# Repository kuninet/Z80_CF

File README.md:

# Z80マイコン コンパクトフラッシュアダプタボード (KZ80-CF)

- SBC8080バスにつながるコンパクトフラッシュボード のデータ類です。
  - [128kB SRAMボード(KZ80-1MSRAM)](https://github.com/kuninet/Z80_1MRAMB)と組み合わせてCP/Mを動かす際に使用できます。
- 詳しい情報は以下のwikiページをご覧ください
  - https://github.com/kuninet/Z80_CF/wiki

## 回路図

[PDF版回路図はこちら](img/SBC80-CF.pdf)

## 部品表

- 部品表は以下にあります。OpenOffice等のcalcで開ける形式です
  - https://github.com/kuninet/Z80_CF/blob/master/KiCAD/SBC80-CF.ods

## 注意点

- REV1基板はコネクタのピンが誤って逆になっているため、CFカードの表裏を逆に挿入する必要があります。(ガイドのレールを削らないとうまくささりません) REV2では改善しています。
- CFカードコネクタは、REV1では秋月電子で手に入るネジ幅40mmのタイプを使用していますが、REV2ではマルツパーツ、aitendoで手に入るネジ幅38.78mmのタイプへ変更しています。

## ライセンス

- 本リポジトリのデータは MIT License のもとで公開します。

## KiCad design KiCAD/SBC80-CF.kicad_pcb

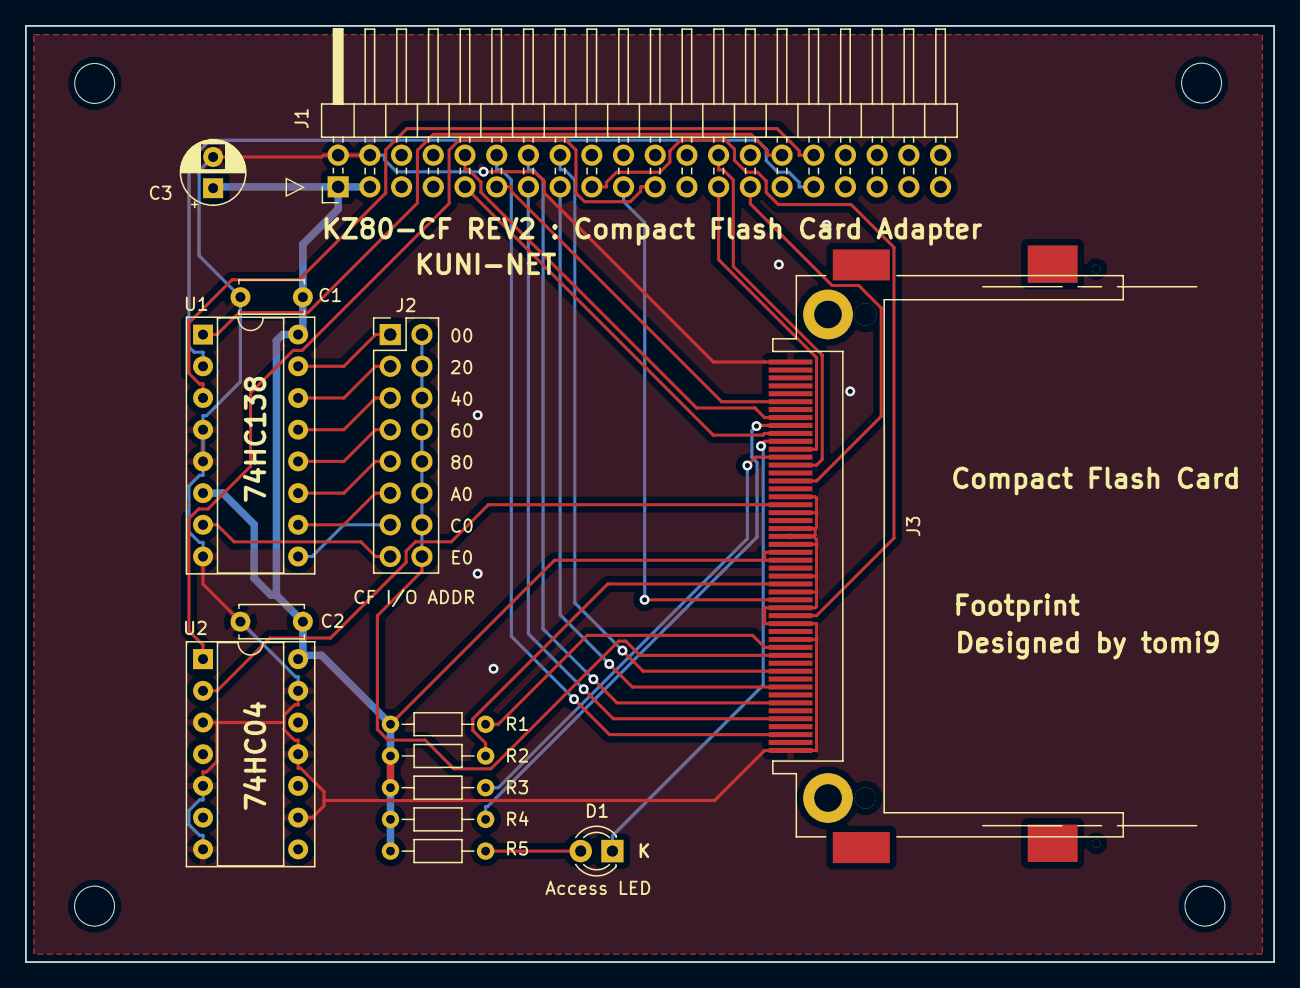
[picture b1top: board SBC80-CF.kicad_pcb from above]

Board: 2 copper layers, 100.0 x 75.0 mm, 18 parts (0 on the bottom side), 35 nets.

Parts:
C1, C2: 0.1u; C_Disc_D5.0mm_W2.5mm_P5.00mm
C3: 10u; CP_Radial_D5.0mm_P2.50mm
D1: LED; LED_D3.0mm
J1: Conn_02x20_Odd_Even; PinHeader_2x20_P2.54mm_Horizontal
J2: I/O ADDR JP; PinHeader_2x08_P2.54mm_Vertical
J3: CF Card Conn; CF-50P
MH1, MH2, MH3, MH4: MountingHole; MountingHole_3.2mm_M3
R1, R2, R3, R4, R5: 1k; R_Axial_DIN0204_L3.6mm_D1.6mm_P7.62mm_Horizontal
U1: 74HC138; DIP-16_W7.62mm_Socket
U2: 74HC04; DIP-14_W7.62mm_Socket

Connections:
/A0: J1.25, J3.20
/A1: J1.26, J3.19
/A2: J1.27, J3.18
/A5: J1.30, U1.1
/A6: J1.31, U1.2
/A7: J1.32, U1.3
/D0: J1.9, J3.21
/D1: J1.10, J3.22
/D2: J1.11, J3.23
/D3: J1.12, J3.2
/D4: J1.13, J3.3
/D5: J1.14, J3.4
/D6: J1.15, J3.5
/D7: J1.16, J3.6
/RES: J1.21, U2.1
/~CS0: J2.2, J2.4, J2.6, J2.8, J2.10, J2.12, J2.14, J2.16, J3.7
/~CS1: J3.32, R1.2
/~DASP: D1.1, J3.45
/~DMACK: J3.44, R3.2
/~PDIAG: J3.46, R4.2
/~WE: J3.36, R2.2
GND: C1.2, C2.2, C3.2, J1.2, J1.4, J3.1, J3.8, J3.9, J3.10, J3.11, J3.12, J3.14, J3.15, J3.16, J3.17, J3.39, J3.50, U1.4, U1.5, U1.8, U2.3, U2.5, U2.7, U2.9, U2.11, U2.13
unnamed: D1.2, R5.2
unnamed: J2.1, U1.15
unnamed: J2.3, U1.14
unnamed: J2.5, U1.13
unnamed: J2.7, U1.12
unnamed: J2.9, U1.11
unnamed: J2.11, U1.10
unnamed: J2.13, U1.9
unnamed: J2.15, U1.7
VCC: C1.1, C2.1, C3.1, J1.1, J1.3, J3.13, J3.38, R1.1, R2.1, R3.1, R4.1, R5.1, U1.6, U1.16, U2.14
~IORD: J1.17, J3.34
~IOWR: J1.19, J3.35
~RESET: J3.41, U2.2

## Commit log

2018-12-13 init commit
2018-12-13 KiCADデータ・ディレクトリ移動
2018-12-13 README追加
2018-12-13 Create LICENSE
2018-12-13 回路図等追加
2018-12-24 CFカード部品変更 REV2基板整備
2018-12-28 部品表整備
2018-12-28 回路図リビジョン更新
2019-01-02 README追記
2019-01-10 シルクパターン等整備
